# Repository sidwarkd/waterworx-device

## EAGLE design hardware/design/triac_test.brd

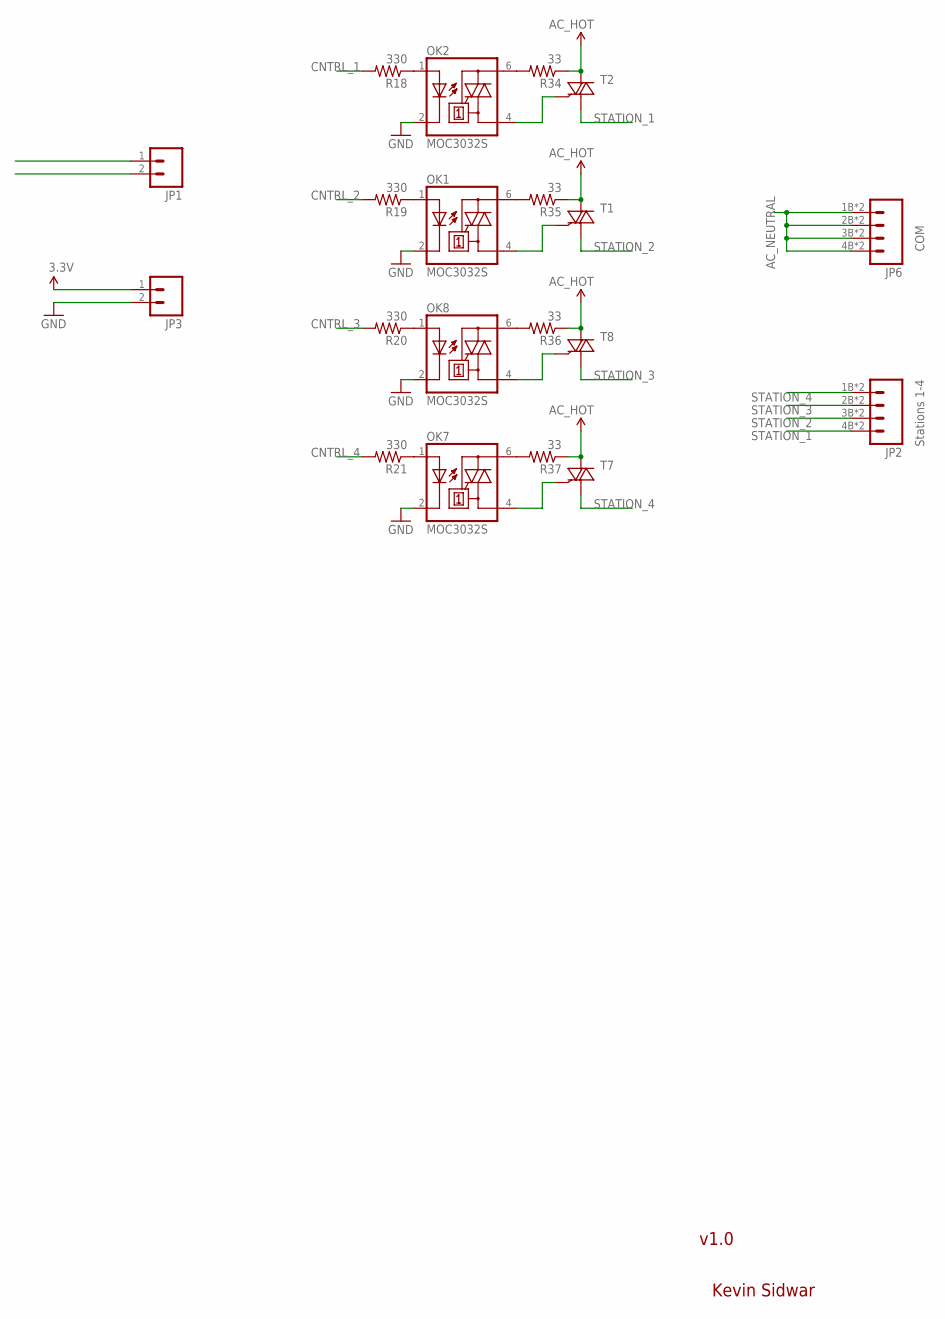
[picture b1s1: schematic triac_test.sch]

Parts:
JP1, JP3: M02LOCK; 1X02_LOCK
JP2: Stations 1-4; PHOENIX_TERMINAL_4
JP6: COM; PHOENIX_TERMINAL_4
OK1, OK2, OK7, OK8: MOC3032S; DIL6-SMD
R18, R19, R20, R21: 330; 0603-RES
R34, R35, R36, R37: 33; 0603-RES
T1, T2, T7, T8: LF-TRIACSOT223; SOT223

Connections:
3.3V: JP3.1
AC_HOT: JP1.1, R34.1, R35.1, R36.1, R37.1, T1.2 (A2), T2.2 (A2), T7.2 (A2), T8.2 (A2)
AC_NEUTRAL: JP1.2, JP6.1B (1), JP6.1T (1), JP6.2B (2), JP6.2T (2), JP6.3B (3), JP6.3T (3), JP6.4B (4), JP6.4T (4)
CNTRL_1: R18.2
CNTRL_2: R19.2
CNTRL_3: R20.2
CNTRL_4: R21.2
GND: JP3.2, OK1.2 (C), OK2.2 (C), OK7.2 (C), OK8.2 (C)
unnamed: OK1.1 (A), R19.1
unnamed: OK1.6 (A2), R35.2
unnamed: OK1.4 (A1), T1.3 (G)
unnamed: OK2.1 (A), R18.1
unnamed: OK2.6 (A2), R34.2
unnamed: OK2.4 (A1), T2.3 (G)
unnamed: OK7.1 (A), R21.1
unnamed: OK7.6 (A2), R37.2
unnamed: OK7.4 (A1), T7.3 (G)
unnamed: OK8.1 (A), R20.1
unnamed: OK8.6 (A2), R36.2
unnamed: OK8.4 (A1), T8.3 (G)
STATION_1: JP2.4B (4), JP2.4T (4), T2.1 (A1)
STATION_2: JP2.3B (3), JP2.3T (3), T1.1 (A1)
STATION_3: JP2.2B (2), JP2.2T (2), T8.1 (A1)
STATION_4: JP2.1B (1), JP2.1T (1), T7.1 (A1)

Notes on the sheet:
Kevin Sidwar
v1.0

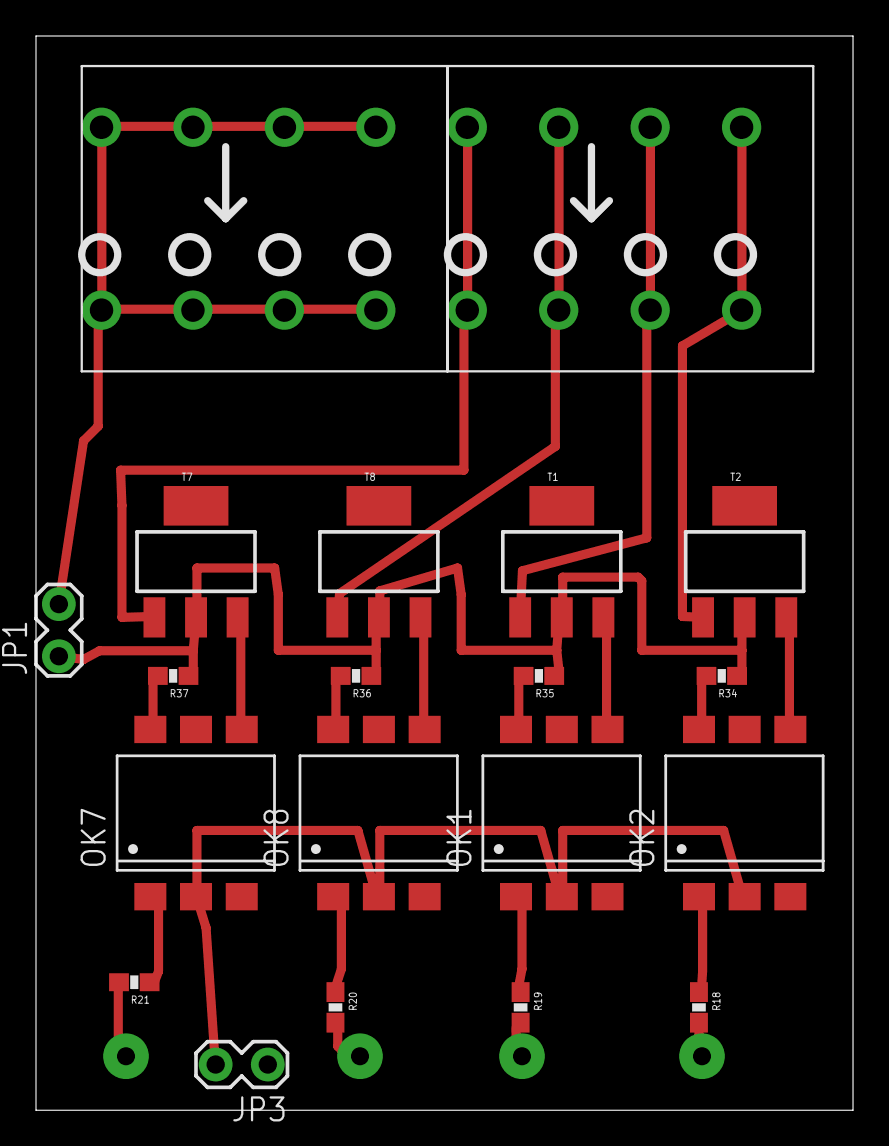
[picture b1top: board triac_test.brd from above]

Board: 2 copper layers, 45.4 x 59.7 mm, 20 parts (0 on the bottom side), 19 nets.

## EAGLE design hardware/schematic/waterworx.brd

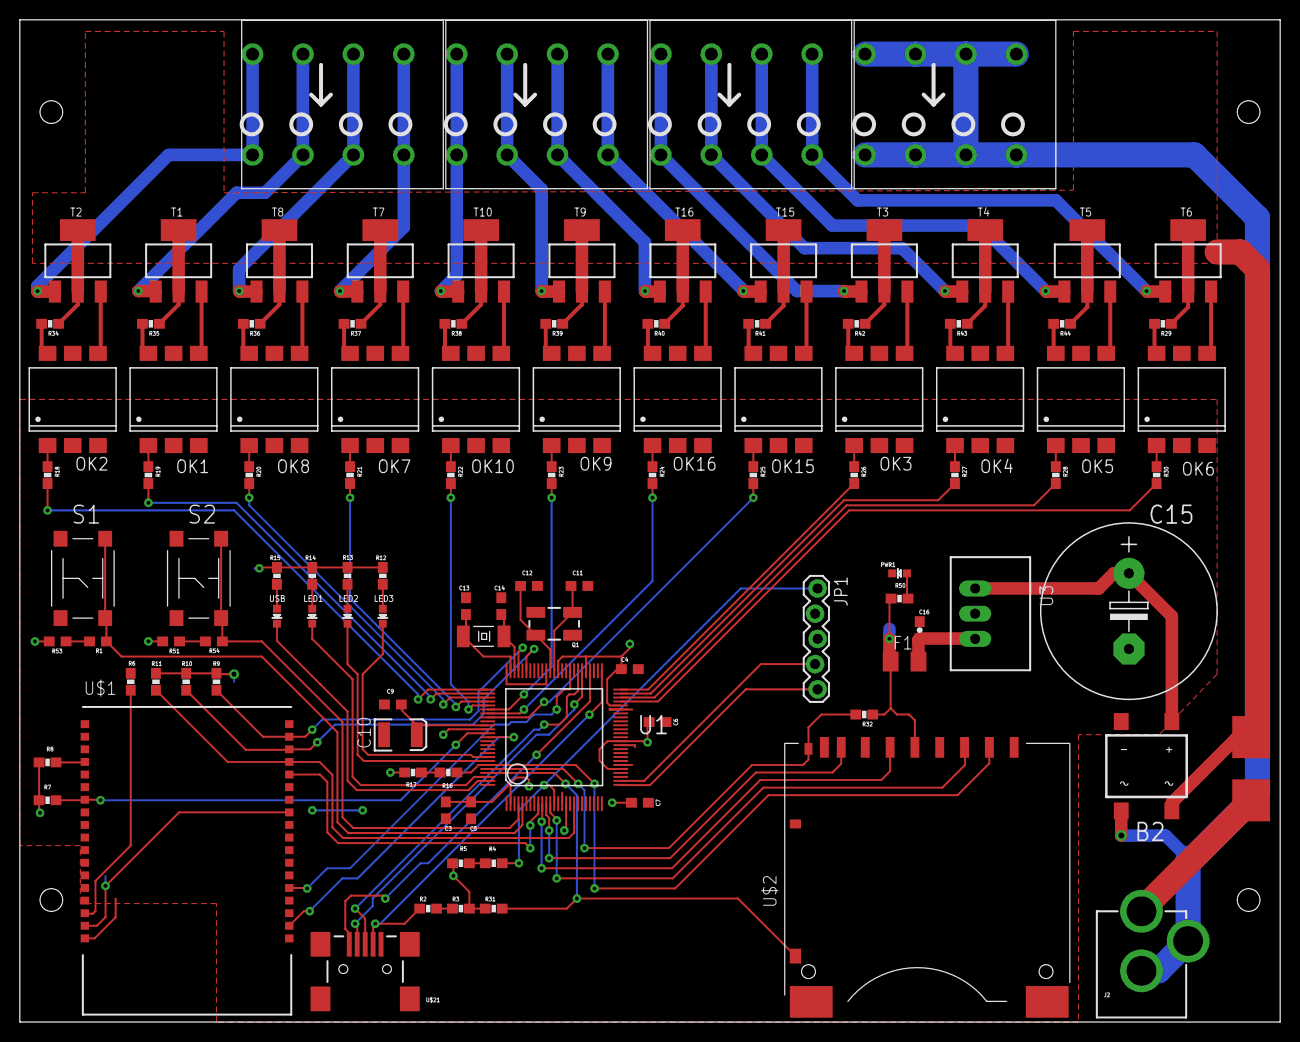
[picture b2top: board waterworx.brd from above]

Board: 2 copper layers, 127.0 x 101.0 mm, 107 parts (0 on the bottom side), 110 nets.

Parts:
B2: DF01S; DFS
C3, C4, C5, C6, C7, C9: 0.1uF; 0603
C10: 10uF; EIA3528
C11, C12: 18pF; 0603
C13, C14: 11pf; 0603
C15: 1000uF; E7,5-18
C16: 1uF; 0603-CAP
F1: 500mA PTC Fuse; M1206
F2: NANO2_HOLDER
J2: POWER_JACKPTH; POWER_JACK_PTH
JP1: 1X05_LOCK
JP2: Stations 1-4; PHOENIX_TERMINAL_4
JP3: Stations 5-8; PHOENIX_TERMINAL_4
JP4: Stations 9-12; PHOENIX_TERMINAL_4
JP6: COM; PHOENIX_TERMINAL_4
LED1: WHITE; LED-0603
LED2: RED; LED-0603
LED3: YELLOW; LED-0603
OK1, OK2, OK3, OK4, OK5, OK6, OK7, OK8, OK9, OK10, OK15, OK16: MOC3032S; DIL6-SMD
PWR1: BLUE; LED-0603
Q1: 8MHz; CRYSTAL-SMD-5X3
Q2: 32.768 KHz; CRYSTAL-SMD-4X2
R1, R51, R53, R54: 4.7K; 0603
R2, R3, R4, R5, R6, R7, R8, R9, R10, R11, R16, R17, R31, R32: 4.7K; 0603-RES
R12, R13, R14, R15, R18, R19, R20, R21, R22, R23, R24, R25, R26, R27, R28, R30, R50: 330; 0603-RES
R29, R34, R35, R36, R37, R38, R39, R40, R41, R42, R43, R44: 33; 0603-RES
S1: S1; SWITCH-OMRON
S2: SWITCH-OMRON
T1, T2, T3, T4, T5, T6, T7, T8, T9, T10, T15, T16: LF-TRIACSOT223; SOT223
U1: PIC32MX460F512L TQFP100; TQFP100
U3: RECOM_X.X_REG78XX; RECOM
U$1: MRF24WB0MA; SMD_MRF
U$2: SD_CARD_SOCKETALPS; SD_ALPS
U$21: USB-MINIB-5PIN; USB-MINIB
USB: GREEN; LED-0603

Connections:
3.3V: C3.1, C4.1, C5.1, C6.1, C7.1, F1.1, JP1.2, R3.2, R5.1, R7.2, R8.1, R9.2, R10.2, R11.2, R12.2, R13.2, R14.2, R15.2, R17.2, R31.1, R32.1, R50.2, R51.2, R53.2, U1.2, U1.16, U1.30, U1.37, U1.46, U1.55, U1.62, U1.86, U$1.17, U$1.29, U$2.4
AC_HOT: B2.AC1, F2.2, R29.1, R34.1, R35.1, R36.1, R37.1, R38.1, R39.1, R40.1, R41.1, R42.1, R43.1, R44.1, T1.2, T1.4, T2.2, T2.4, T3.2, T3.4, T4.2, T4.4, T5.2, T5.4, T6.2, T6.4, T7.2, T7.4, T8.2, T8.4, T9.2, T9.4, T10.2, T10.4, T15.2, T15.4, T16.2, T16.4
AC_NEUTRAL: B2.AC2, J2.GND, J2.GNDBREAK, JP6.1B, JP6.1T, JP6.2B, JP6.2T, JP6.3B, JP6.3T, JP6.4B, JP6.4T
CNTRL_1: R18.2, U1.76
CNTRL_2: R19.2, U1.77
CNTRL_3: R20.2, U1.78
CNTRL_4: R21.2, U1.79
CNTRL_5: R22.2, U1.80
CNTRL_6: R23.2, U1.81
CNTRL_7: R24.2, U1.82
CNTRL_8: R25.2, U1.83
CNTRL_9: R26.2, U1.50
CNTRL_10: R27.2, U1.49
CNTRL_11: R28.2, U1.48
CNTRL_12: R30.2, U1.47
D+: U1.57, U$21.D+
D-: U1.56, U$21.D-
GND: B2.-, C3.2, C4.2, C5.2, C6.2, C7.2, C9.2, C10.C, C11.1, C12.1, C13.2, C14.2, C15.-, C16.2, JP1.3, OK1.2, OK2.2, OK3.2, OK4.2, OK5.2, OK6.2, OK7.2, OK8.2, OK9.2, OK10.2, OK15.2, OK16.2, PWR1.C, R6.1, S1.1, S1.2, S2.1, S2.2, U1.15, U1.31, U1.36, U1.45, U1.65, U1.75, U3.GND, U$1.1, U$1.10, U$1.18, U$1.19, U$1.25, U$1.28, U$1.30, U$1.36, U$2.3, U$2.6, U$2.12, U$2.VSS, U$21.GND, U$21.MTN1, U$21.MTN2, U$21.MTN3, U$21.MTN4
unnamed: OK9.1, R23.1
unnamed: OK1.1, R19.1
unnamed: R51.1, R54.1
unnamed: R1.1, R53.1
unnamed: R8.2, U$1.4
unnamed: OK1.6, R35.2
unnamed: OK9.6, R39.2
unnamed: OK1.4, T1.3
unnamed: OK2.1, R18.1
unnamed: R16.1, R17.1
unnamed: R4.2, R5.2
unnamed: OK2.6, R34.2
unnamed: OK9.4, T9.3
unnamed: OK2.4, T2.3
unnamed: R2.2, R3.1
unnamed: B2.+, C15.+, U3.VIN
unnamed: OK3.1, R26.1
unnamed: OK3.6, R42.2
unnamed: PWR1.A, R50.1
unnamed: R15.1, USB.A
unnamed: OK3.4, T3.3
unnamed: LED1.A, R14.1
unnamed: LED2.A, R13.1
unnamed: C16.1, F1.2, U3.VOUT
unnamed: OK6.1, R30.1
unnamed: OK4.1, R27.1
unnamed: OK4.6, R43.2
unnamed: OK10.1, R22.1
unnamed: OK4.4, T4.3
unnamed: OK6.6, R29.2
unnamed: OK6.4, T6.3
unnamed: OK5.1, R28.1
unnamed: OK5.6, R44.2
unnamed: OK10.6, R38.2
unnamed: LED3.A, R12.1
unnamed: OK5.4, T5.3
unnamed: F2.1, J2.PWR
unnamed: OK10.4, T10.3
unnamed: OK7.1, R21.1
unnamed: OK7.6, R37.2
unnamed: OK7.4, T7.3
unnamed: OK8.1, R20.1
unnamed: OK8.6, R36.2
unnamed: OK8.4, T8.3
unnamed: OK15.1, R25.1
unnamed: OK15.6, R41.2
unnamed: OK15.4, T15.3
unnamed: OK16.1, R24.1
unnamed: OK16.6, R40.2
unnamed: OK16.4, T16.3
unnamed: C9.1, C10.A, U1.85
OSC1: C11.2, Q1.1, U1.63
OSC2: C12.2, Q1.3, U1.64
PGC: JP1.5, U1.26
PGD: JP1.4, U1.27
RC13: C14.1, Q2.P$2, U1.73
RC14: C13.1, Q2.P$1, U1.74
RE0: LED3.C, U1.93
RE1: LED2.C, U1.94
RE2: LED1.C, U1.98
RE3: U1.99, USB.C
RE6: R54.2, S2.3, S2.4, U1.4
RE7: R1.2, S1.3, S1.4, U1.5
SD_CD: R32.2, U1.96, U$2.CD
SD_CK: U1.10, U$2.5
SD_CS: R16.2, U1.95, U$2.1
SD_DI: U1.12, U$2.2
SD_DO: U1.11, U$2.7
SD_WP: R31.2, U1.97, U$2.WP
STATION_1: JP2.1B, JP2.1T, T2.1
STATION_2: JP2.2B, JP2.2T, T1.1
STATION_3: JP2.3B, JP2.3T, T8.1
STATION_4: JP2.4B, JP2.4T, T7.1
STATION_5: JP3.1B, JP3.1T, T10.1
STATION_6: JP3.2B, JP3.2T, T9.1
STATION_7: JP3.3B, JP3.3T, T16.1
STATION_8: JP3.4B, JP3.4T, T15.1
STATION_9: JP4.1B, JP4.1T, T3.1
STATION_10: JP4.2B, JP4.2T, T4.1
STATION_11: JP4.3B, JP4.3T, T5.1
STATION_12: JP4.4B, JP4.4T, T6.1
USBID: R2.1, U1.51, U$21.ID
VBUS: U1.54, U$21.VBUS
VPP: JP1.1, R4.1, U1.13
WF_CK: R10.1, U1.70, U$1.34
WF_CS: U1.59, U$1.23
WF_DI: R9.1, U1.72, U$1.35
WF_DO: U1.9, U$1.32
WF_HIBERNATE: U1.88, U$1.20
WF_INT: R11.1, U1.18, U$1.33
WF_RESET: R7.1, U1.87, U$1.7
WF_WP: R6.2, U$1.16

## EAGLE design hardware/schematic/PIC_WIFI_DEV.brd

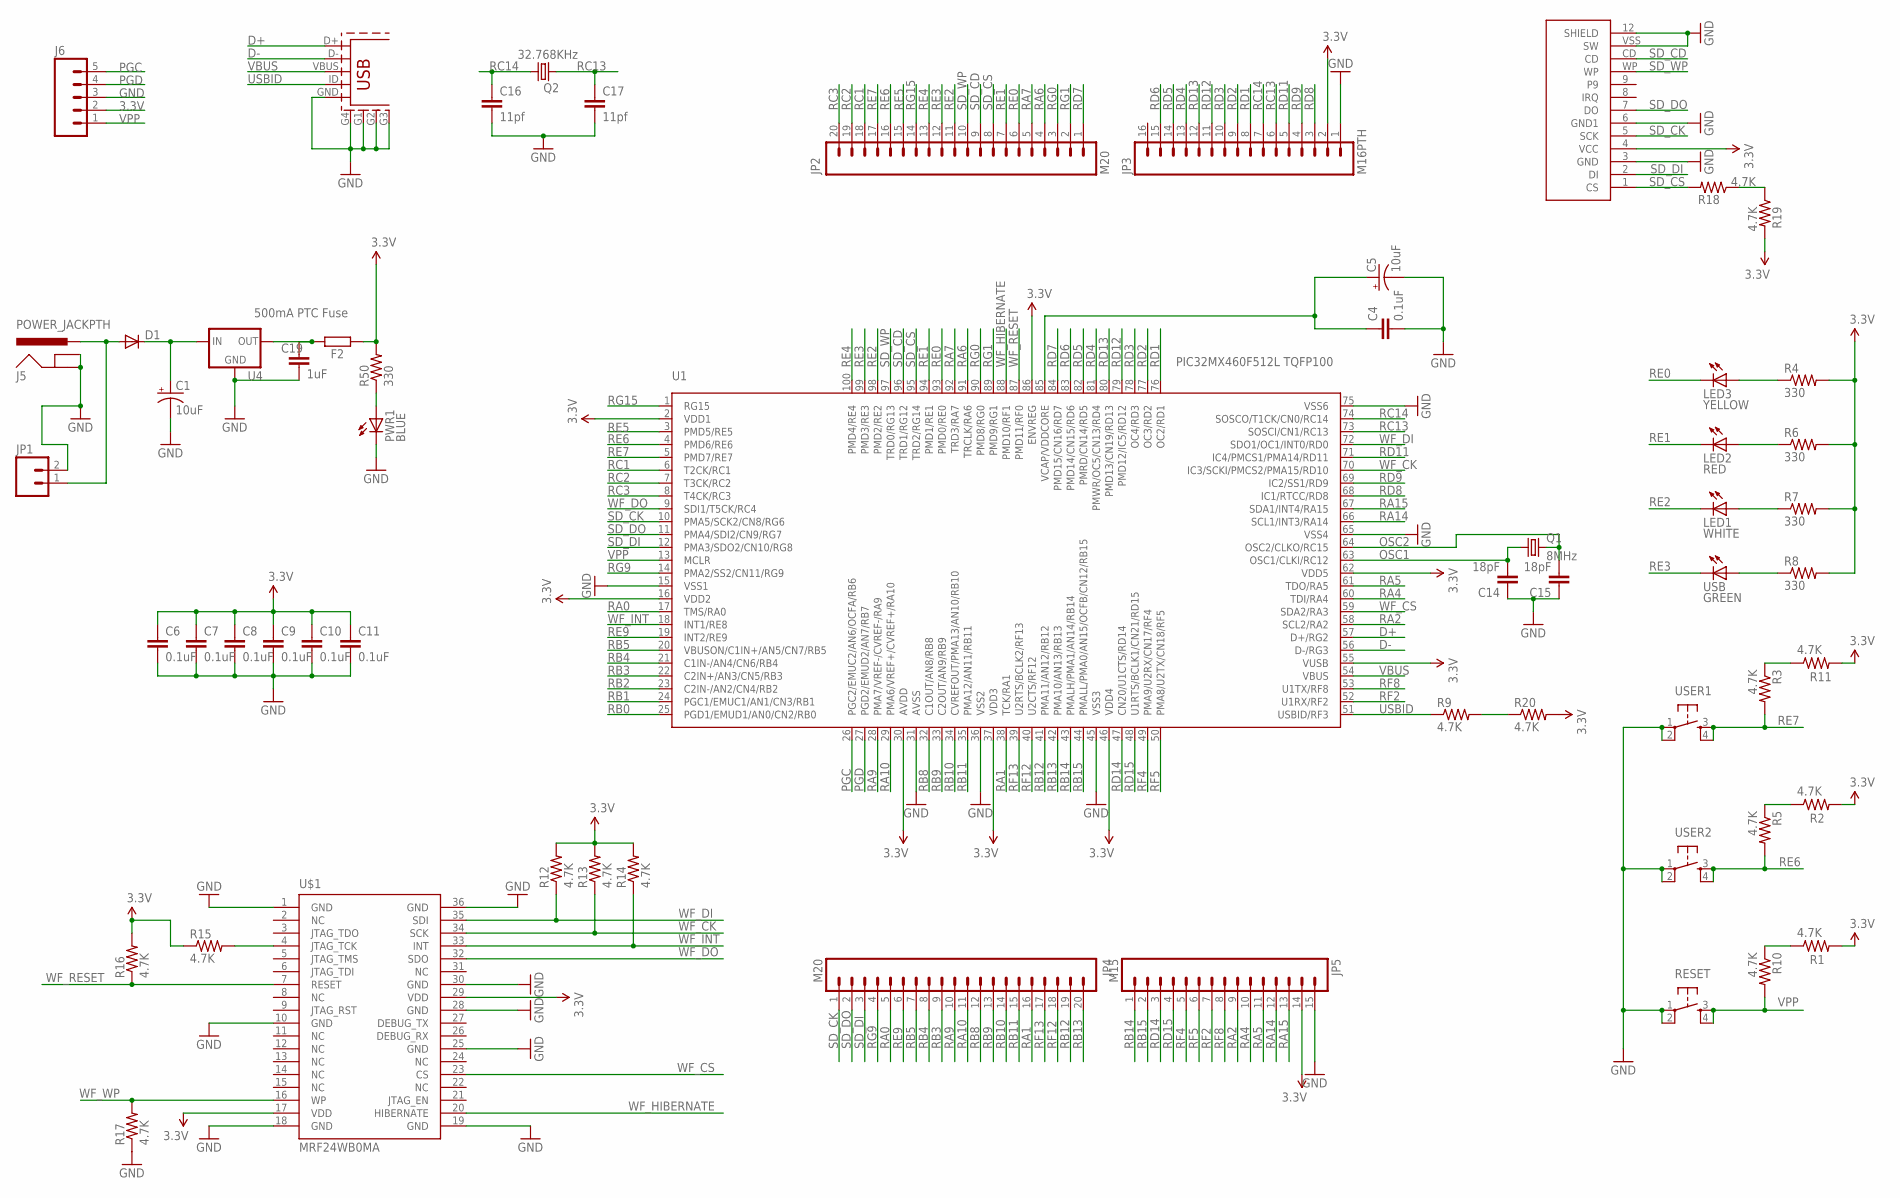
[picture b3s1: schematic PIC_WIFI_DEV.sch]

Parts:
C1, C5: 10uF; EIA3528
C4, C6, C7, C8, C9, C10, C11: 0.1uF; C0402
C14, C15: 18pF; C0402
C16, C17: 11pf; C0402
C19: 1uF; 0603-CAP
D1: DIODESMA; SMA-DIODE
F2: 500mA PTC Fuse; M1206
J5: POWER_JACKPTH; POWER_JACK_PTH
J6: M05PTH; 1X05
J8: USB_5PIN; USB-MINIB
JP1: M02PTH; 1X02
JP2, JP4: M20; 1X20
JP3: M16PTH; 1X16
JP5: M15; 1X15
LED1: WHITE; LED-0603
LED2: RED; LED-0603
LED3: YELLOW; LED-0603
PWR1: BLUE; LED-0603
Q1: 8MHz; CRYSTAL-SMD-5X3
Q2: 32.768KHz; CRYSTAL-SMD-4X2
R1, R2, R3, R5, R9, R10, R11, R20: 4.7K; C0402
R4, R6, R7, R8: 330; C0402
R12, R13, R14, R15, R16, R17, R18, R19: 4.7K; 0603-RES
R50: 330; 0603-RES
RESET: TAC_SWITCHB3FS; SWITCH-OMRON
U1: PIC32MX460F512L TQFP100; TQFP100
U4: RECOM_X.X_REG78XX; RECOM
U$1: MRF24WB0MA; SMD_MRF
U$2: SD_CARD_SOCKETALPS; SD_ALPS
USB: GREEN; LED-0603
USER1, USER2: TAC_SWITCHB3FS; SWITCH-OMRON

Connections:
3.3V: C6.1, C7.1, C8.1, C9.1, C10.1, C11.1, F2.1, J6.2, JP3.2, JP5.14, R1.2, R2.2, R4.2, R6.2, R7.2, R8.2, R11.2, R12.2, R13.2, R14.2, R15.1, R16.2, R19.2, R20.2, R50.2, U1.2 (VDD1), U1.16 (VDD2), U1.30 (AVDD), U1.37 (VDD3), U1.46 (VDD4), U1.55 (VUSB), U1.62 (VDD5), U1.86 (ENVREG), U$1.17 (VDD), U$1.29 (VDD), U$2.4 (VCC)
D+: J8.D+, U1.57 (D+/RG2)
D-: J8.D-, U1.56 (D-/RG3)
GND: C1.C (-), C4.2, C5.C (-), C6.2, C7.2, C8.2, C9.2, C10.2, C11.2, C14.1, C15.1, C16.2, C17.2, C19.2, J5.GND, J5.GNDBREAK, J6.3, J8.G1, J8.G2, J8.G3, J8.G4 (SHIELD), J8.GND, JP1.2, JP3.1, JP5.15, PWR1.C, R17.1, RESET.1, RESET.2, U1.15 (VSS1), U1.31 (AVSS), U1.36 (VSS2), U1.45 (VSS3), U1.65 (VSS4), U1.75 (VSS6), U4.GND, U$1.1 (GND), U$1.10 (GND), U$1.18 (GND), U$1.19 (GND), U$1.25 (GND), U$1.28 (GND), U$1.30 (GND), U$1.36 (GND), U$2.3 (GND), U$2.6 (GND1), U$2.12 (SHIELD), U$2.VSS (SW), USER1.1, USER1.2, USER2.1, USER2.2
unnamed: R1.1, R10.1
unnamed: D1.A, J5.PWR, JP1.1
unnamed: R2.1, R5.1
unnamed: R3.1, R11.1
unnamed: R15.2, U$1.4 (JTAG_TCK)
unnamed: R9.2, R20.1
unnamed: R18.1, R19.1
unnamed: PWR1.A, R50.1
unnamed: R8.1, USB.A
unnamed: LED1.A, R7.1
unnamed: LED2.A, R6.1
unnamed: C19.1, F2.2, U4.VOUT (OUT)
unnamed: LED3.A, R4.1
unnamed: C4.1, C5.A (+), U1.85 (VCAP/VDDCORE)
OSC1: C14.2, Q1.1, U1.63 (OSC1/CLKI/RC12)
OSC2: C15.2, Q1.3 (2), U1.64 (OSC2/CLKO/RC15)
PGC: J6.5, U1.26 (PGC2/EMUC2/AN6/OCFA/RB6)
PGD: J6.4, U1.27 (PGD2/EMUD2/AN7/RB7)
RA0: JP4.5, U1.17 (TMS/RA0)
RA1: JP4.16, U1.38 (TCK/RA1)
RA2: JP5.9, U1.58 (SCL2/RA2)
RA4: JP5.10, U1.60 (TDI/RA4)
RA5: JP5.11, U1.61 (TDO/RA5)
RA6: JP2.4, U1.91 (TRCLK/RA6)
RA7: JP2.5, U1.92 (TRD3/RA7)
RA9: JP4.10, U1.28 (PMA7/VREF-/CVREF-/RA9)
RA10: JP4.11, U1.29 (PMA6/VREF+/CVREF+/RA10)
RA14: JP5.12, U1.66 (SCL1/INT3/RA14)
RA15: JP5.13, U1.67 (SDA1/INT4/RA15)
RB0: U1.25 (PGD1/EMUD1/AN0/CN2/RB0)
RB1: U1.24 (PGC1/EMUC1/AN1/CN3/RB1)
RB2: U1.23 (C2IN-/AN2/CN4/RB2)
RB3: JP4.9, U1.22 (C2IN+/AN3/CN5/RB3)
RB4: JP4.8, U1.21 (C1IN-/AN4/CN6/RB4)
RB5: JP4.7, U1.20 (VBUSON/C1IN+/AN5/CN7/RB5)
RB8: JP4.12, U1.32 (C1OUT/AN8/RB8)
RB9: JP4.13, U1.33 (C2OUT/AN9/RB9)
RB10: JP4.14, U1.34 (CVREFOUT/PMA13/AN10/RB10)
RB11: JP4.15, U1.35 (PMA12/AN11/RB11)
RB12: JP4.19, U1.41 (PMA11/AN12/RB12)
RB13: JP4.20, U1.42 (PMA10/AN13/RB13)
RB14: JP5.1, U1.43 (PMALH/PMA1/AN14/RB14)
RB15: JP5.2, U1.44 (PMALL/PMA0/AN15/OCFB/CN12/RB15)
RC1: JP2.18, U1.6 (T2CK/RC1)
RC2: JP2.19, U1.7 (T3CK/RC2)
RC3: JP2.20, U1.8 (T4CK/RC3)
RC13: C17.1, JP3.6, Q2.P$2 (2), U1.73 (SOSCI/CN1/RC13)
RC14: C16.1, JP3.7, Q2.P$1 (1), U1.74 (SOSCO/T1CK/CN0/RC14)
RD1: JP3.8, U1.76 (OC2/RD1)
RD2: JP3.9, U1.77 (OC3/RD2)
RD3: JP3.10, U1.78 (OC4/RD3)
RD4: JP3.13, U1.81 (PMWR/OC5/CN13/RD4)
RD5: JP3.14, U1.82 (PMRD/CN14/RD5)
RD6: JP3.15, U1.83 (PMD14/CN15/RD6)
RD7: JP2.1, U1.84 (PMD15/CN16/RD7)
RD8: JP3.3, U1.68 (IC1/RTCC/RD8)
RD9: JP3.4, U1.69 (IC2/SS1/RD9)
RD11: JP3.5, U1.71 (IC4/PMCS1/PMA14/RD11)
RD12: JP3.11, U1.79 (PMD12/IC5/RD12)
RD13: JP3.12, U1.80 (PMD13/CN19/RD13)
RD14: JP5.3, U1.47 (CN20/U1CTS/RD14)
RD15: JP5.4, U1.48 (U1RTS/BCLK1/CN21/RD15)
RE0: JP2.6, LED3.C, U1.93 (PMD0/RE0)
RE1: JP2.7, LED2.C, U1.94 (PMD1/RE1)
RE2: JP2.11, LED1.C, U1.98 (PMD2/RE2)
RE3: JP2.12, U1.99 (PMD3/RE3), USB.C
RE4: JP2.13, U1.100 (PMD4/RE4)
RE5: JP2.15, U1.3 (PMD5/RE5)
RE6: JP2.16, R5.2, U1.4 (PMD6/RE6), USER2.3, USER2.4
RE7: JP2.17, R3.2, U1.5 (PMD7/RE7), USER1.3, USER1.4
RE9: JP4.6, U1.19 (INT2/RE9)
RF2: JP5.7, U1.52 (U1RX/RF2)
RF4: JP5.5, U1.49 (PMA9/U2RX/CN17/RF4)
RF5: JP5.6, U1.50 (PMA8/U2TX/CN18/RF5)
RF8: JP5.8, U1.53 (U1TX/RF8)
RF12: JP4.18, U1.40 (U2CTS/RF12)
RF13: JP4.17, U1.39 (U2RTS/BCLK2/RF13)
RG0: JP2.3, U1.90 (PMD8/RG0)
RG1: JP2.2, U1.89 (PMD9/RG1)
RG9: JP4.4, U1.14 (PMA2/SS2/CN11/RG9)
RG15: JP2.14, U1.1 (RG15)
SD_CD: JP2.9, U1.96 (TRD1/RG12), U$2.CD
SD_CK: JP4.1, U1.10 (PMA5/SCK2/CN8/RG6), U$2.5 (SCK)
SD_CS: JP2.8, R18.2, U1.95 (TRD2/RG14), U$2.1 (CS)
SD_DI: JP4.3, U1.12 (PMA3/SDO2/CN10/RG8), U$2.2 (DI)
SD_DO: JP4.2, U1.11 (PMA4/SDI2/CN9/RG7), U$2.7 (DO)
SD_WP: JP2.10, U1.97 (TRD0/RG13), U$2.WP
USBID: J8.ID (USB_ID), R9.1, U1.51 (USBID/RF3)
VBUS: J8.VBUS, U1.54 (VBUS)
VIN_RAW: C1.A (+), D1.C, U4.VIN (IN)
VPP: J6.1, R10.2, RESET.3, RESET.4, U1.13 (MCLR)
WF_CK: R13.1, U1.70 (IC3/SCKI/PMCS2/PMA15/RD10), U$1.34 (SCK)
WF_CS: U1.59 (SDA2/RA3), U$1.23 (CS)
WF_DI: R12.1, U1.72 (SDO1/OC1/INT0/RD0), U$1.35 (SDI)
WF_DO: U1.9 (SDI1/T5CK/RC4), U$1.32 (SDO)
WF_HIBERNATE: U1.88 (PMD10/RF1), U$1.20 (HIBERNATE)
WF_INT: R14.1, U1.18 (INT1/RE8), U$1.33 (INT)
WF_RESET: R16.1, U1.87 (PMD11/RF0), U$1.7 (RESET)
WF_WP: R17.2, U$1.16 (WP)

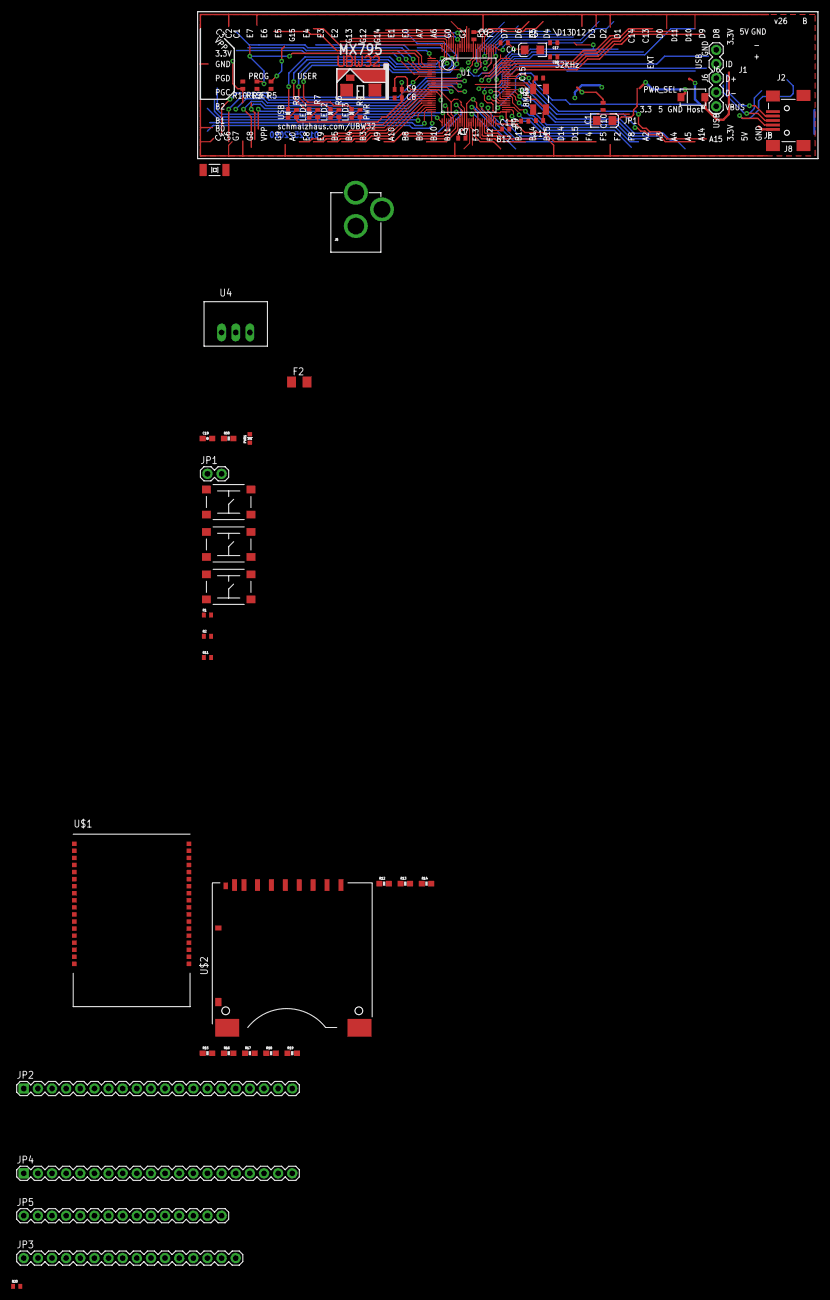
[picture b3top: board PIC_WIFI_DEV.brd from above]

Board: 2 copper layers, 111.5 x 26.4 mm, 61 parts (0 on the bottom side), 100 nets.

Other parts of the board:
U$3: UBW32
U$5: SCHMALZHAUS

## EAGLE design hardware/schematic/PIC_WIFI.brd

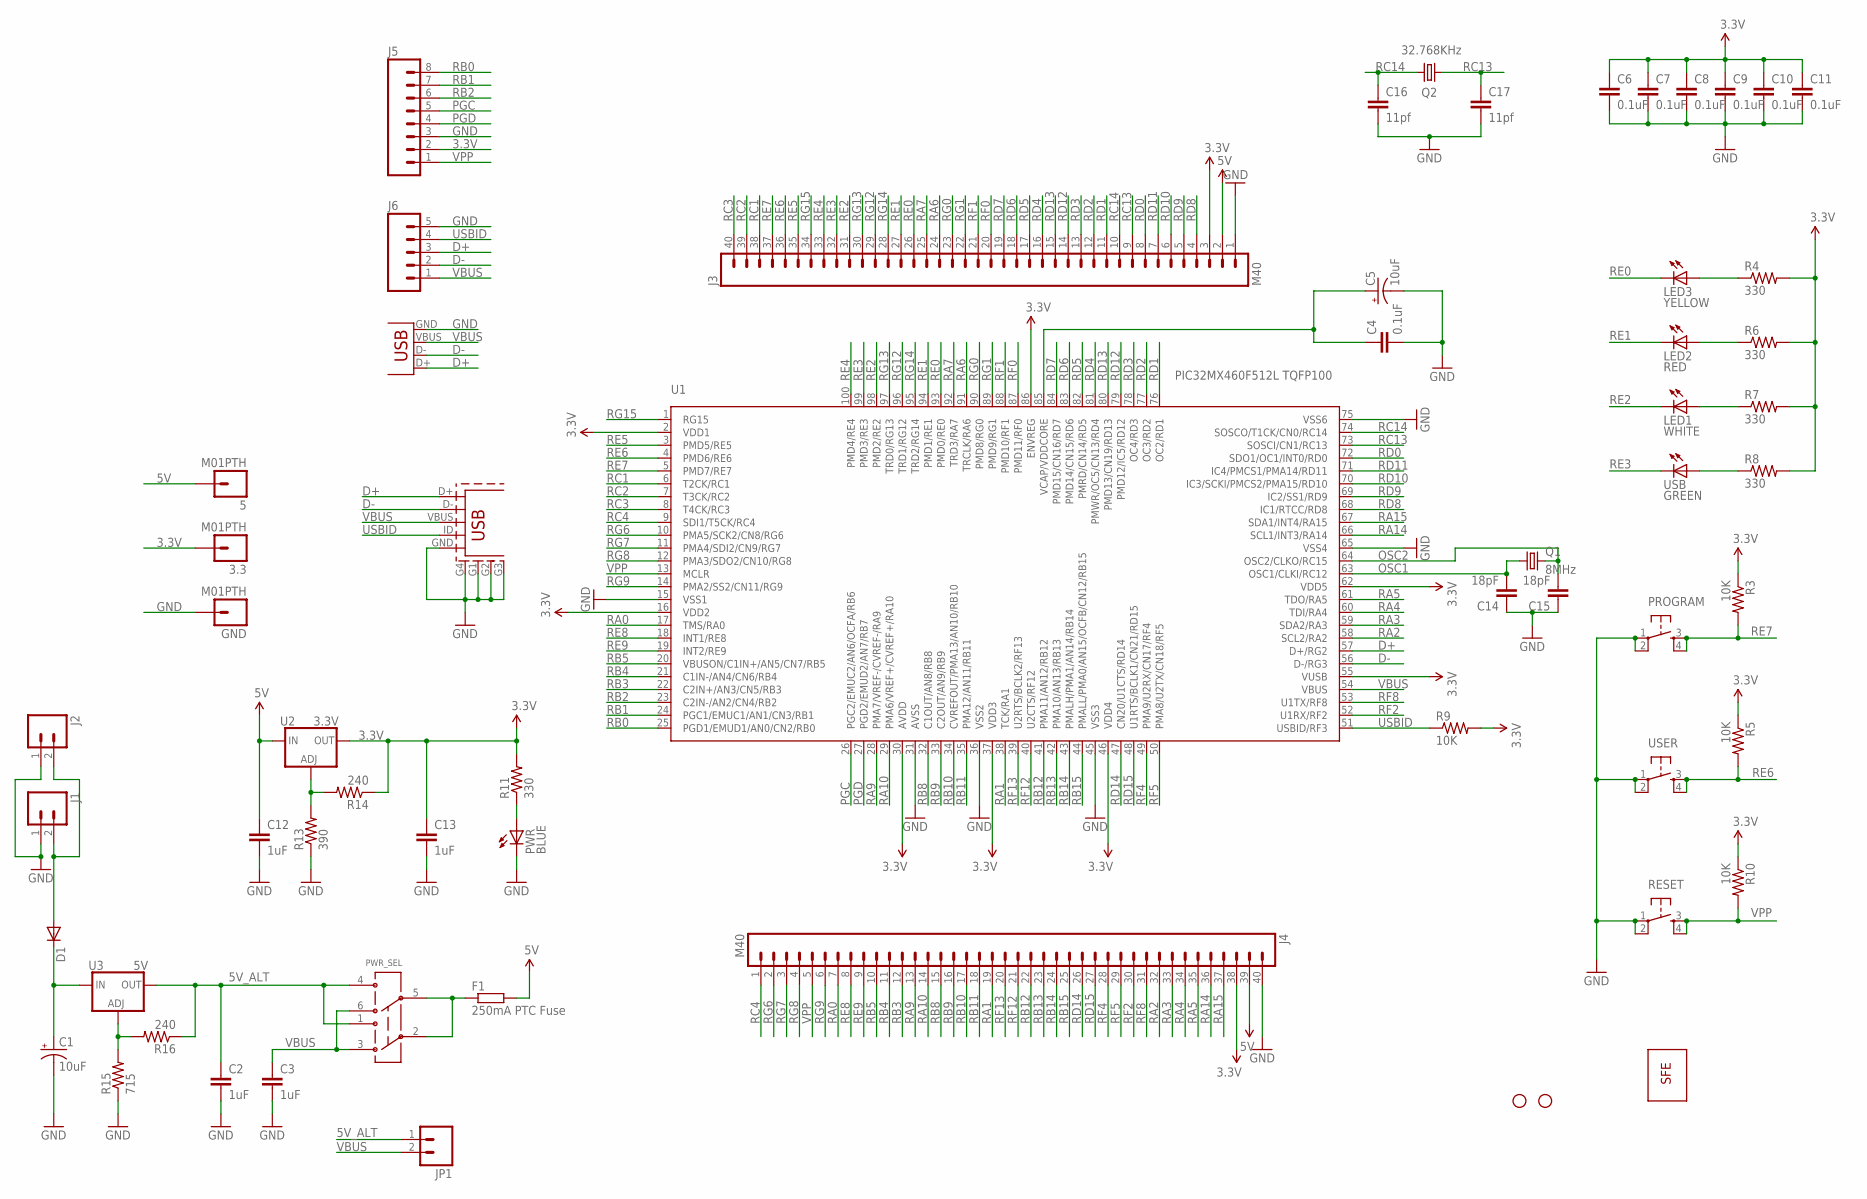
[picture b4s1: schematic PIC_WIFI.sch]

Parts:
3.3, 5: M01PTH; 1X01
C1, C5: 10uF; EIA3528
C2, C3, C12, C13: 1uF; C0402
C4, C6, C7, C8, C9, C10, C11: 0.1uF; C0402
C14, C15: 18pF; C0402
C16, C17: 11pf; C0402
D1: DIODESMA; SMA-DIODE
F1: 250mA PTC Fuse; R1206
GND: M01PTH; 1X01
J1: M02PTH; 1X02
J2: M02-JST-2MM-SMT; S2B-PH
J3, J4: M40; 1X40
J5: M08; 1X08
J6: M05PTH; 1X05
J7: USB-A-S
J8: USB_5PIN; USB-MINIB
JP1: M02PTH; 1X02
LED1: WHITE; LED-0603
LED2: RED; LED-0603
LED3: YELLOW; LED-0603
PROGRAM: TAC_SWITCHSND; TACTILE_SWITCH_SMD
PWR: BLUE; LED-0603
PWR_SEL: AYZ0202
Q1: 8MHz; CRYSTAL-SMD-5X3
Q2: 32.768KHz; CRYSTAL-32KHZ-SMD
R3, R5, R9, R10: 10K; C0402
R4, R6, R7, R8, R11: 330; C0402
R13: 390; C0402
R14, R16: 240; C0402
R15: 715; C0402
RESET: TAC_SWITCHSND; TACTILE_SWITCH_SMD
U1: PIC32MX460F512L TQFP100; TQFP100
U2: 3.3V; SOT223
U3: 5V; SOT223
U$4: LOGO-SFENEW; SFE-NEW-WEBLOGO
U$6, U$7: STAND-OFF
USB: GREEN; LED-0603
USER: TAC_SWITCHSND; TACTILE_SWITCH_SMD

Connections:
3.3V: 3.3.1, C6.1, C7.1, C8.1, C9.1, C10.1, C11.1, C13.1, J3.3, J4.38, J5.2, R3.1, R4.2, R5.1, R6.2, R7.2, R8.2, R9.2, R10.1, R11.2, R14.1, U1.2 (VDD1), U1.16 (VDD2), U1.30 (AVDD), U1.37 (VDD3), U1.46 (VDD4), U1.55 (VUSB), U1.62 (VDD5), U1.86 (ENVREG), U2.2 (OUT)
5V: 5.1, C12.1, F1.2, J3.2, J4.39, U2.3 (IN)
5V_ALT: C2.1, JP1.1, PWR_SEL.1 (3), PWR_SEL.4 (6), R16.1, U3.2 (OUT)
D+: J6.3, J7.D+, J8.D+, U1.57 (D+/RG2)
D-: J6.2, J7.D-, J8.D-, U1.56 (D-/RG3)
GND: C1.C (-), C2.2, C3.2, C4.2, C5.C (-), C6.2, C7.2, C8.2, C9.2, C10.2, C11.2, C12.2, C13.2, C14.1, C15.1, C16.2, C17.2, GND.1, J1.1, J2.1, J3.1, J4.40, J5.3, J6.5, J7.GND, J8.G1, J8.G2, J8.G3, J8.G4 (SHIELD), J8.GND, PROGRAM.1, PROGRAM.2, PWR.C, R13.1, R15.1, RESET.1, RESET.2, U1.15 (VSS1), U1.31 (AVSS), U1.36 (VSS2), U1.45 (VSS3), U1.65 (VSS4), U1.75 (VSS6), USER.1, USER.2
unnamed: D1.A, J1.2, J2.2
unnamed: F1.1, PWR_SEL.2, PWR_SEL.5
unnamed: R13.2, R14.2, U2.1 (ADJ)
unnamed: R15.2, R16.2, U3.1 (ADJ)
unnamed: PWR.A, R11.1
unnamed: R8.1, USB.A
unnamed: LED1.A, R7.1
unnamed: LED2.A, R6.1
unnamed: LED3.A, R4.1
unnamed: C4.1, C5.A (+), U1.85 (VCAP/VDDCORE)
OSC1: C14.2, Q1.1, U1.63 (OSC1/CLKI/RC12)
OSC2: C15.2, Q1.3 (2), U1.64 (OSC2/CLKO/RC15)
PGC: J5.5, U1.26 (PGC2/EMUC2/AN6/OCFA/RB6)
PGD: J5.4, U1.27 (PGD2/EMUD2/AN7/RB7)
RA0: J4.7, U1.17 (TMS/RA0)
RA1: J4.19, U1.38 (TCK/RA1)
RA2: J4.32, U1.58 (SCL2/RA2)
RA3: J4.33, U1.59 (SDA2/RA3)
RA4: J4.34, U1.60 (TDI/RA4)
RA5: J4.35, U1.61 (TDO/RA5)
RA6: J3.24, U1.91 (TRCLK/RA6)
RA7: J3.25, U1.92 (TRD3/RA7)
RA9: J4.13, U1.28 (PMA7/VREF-/CVREF-/RA9)
RA10: J4.14, U1.29 (PMA6/VREF+/CVREF+/RA10)
RA14: J4.36, U1.66 (SCL1/INT3/RA14)
RA15: J4.37, U1.67 (SDA1/INT4/RA15)
RB0: J5.8, U1.25 (PGD1/EMUD1/AN0/CN2/RB0)
RB1: J5.7, U1.24 (PGC1/EMUC1/AN1/CN3/RB1)
RB2: J5.6, U1.23 (C2IN-/AN2/CN4/RB2)
RB3: J4.12, U1.22 (C2IN+/AN3/CN5/RB3)
RB4: J4.11, U1.21 (C1IN-/AN4/CN6/RB4)
RB5: J4.10, U1.20 (VBUSON/C1IN+/AN5/CN7/RB5)
RB8: J4.15, U1.32 (C1OUT/AN8/RB8)
RB9: J4.16, U1.33 (C2OUT/AN9/RB9)
RB10: J4.17, U1.34 (CVREFOUT/PMA13/AN10/RB10)
RB11: J4.18, U1.35 (PMA12/AN11/RB11)
RB12: J4.22, U1.41 (PMA11/AN12/RB12)
RB13: J4.23, U1.42 (PMA10/AN13/RB13)
RB14: J4.24, U1.43 (PMALH/PMA1/AN14/RB14)
RB15: J4.25, U1.44 (PMALL/PMA0/AN15/OCFB/CN12/RB15)
RC1: J3.38, U1.6 (T2CK/RC1)
RC2: J3.39, U1.7 (T3CK/RC2)
RC3: J3.40, U1.8 (T4CK/RC3)
RC4: J4.1, U1.9 (SDI1/T5CK/RC4)
RC13: C17.1, J3.9, Q2.X1 (1), U1.73 (SOSCI/CN1/RC13)
RC14: C16.1, J3.10, Q2.X2 (2), U1.74 (SOSCO/T1CK/CN0/RC14)
RD0: J3.8, U1.72 (SDO1/OC1/INT0/RD0)
RD1: J3.11, U1.76 (OC2/RD1)
RD2: J3.12, U1.77 (OC3/RD2)
RD3: J3.13, U1.78 (OC4/RD3)
RD4: J3.16, U1.81 (PMWR/OC5/CN13/RD4)
RD5: J3.17, U1.82 (PMRD/CN14/RD5)
RD6: J3.18, U1.83 (PMD14/CN15/RD6)
RD7: J3.19, U1.84 (PMD15/CN16/RD7)
RD8: J3.4, U1.68 (IC1/RTCC/RD8)
RD9: J3.5, U1.69 (IC2/SS1/RD9)
RD10: J3.6, U1.70 (IC3/SCKI/PMCS2/PMA15/RD10)
RD11: J3.7, U1.71 (IC4/PMCS1/PMA14/RD11)
RD12: J3.14, U1.79 (PMD12/IC5/RD12)
RD13: J3.15, U1.80 (PMD13/CN19/RD13)
RD14: J4.26, U1.47 (CN20/U1CTS/RD14)
RD15: J4.27, U1.48 (U1RTS/BCLK1/CN21/RD15)
RE0: J3.26, LED3.C, U1.93 (PMD0/RE0)
RE1: J3.27, LED2.C, U1.94 (PMD1/RE1)
RE2: J3.31, LED1.C, U1.98 (PMD2/RE2)
RE3: J3.32, U1.99 (PMD3/RE3), USB.C
RE4: J3.33, U1.100 (PMD4/RE4)
RE5: J3.35, U1.3 (PMD5/RE5)
RE6: J3.36, R5.2, U1.4 (PMD6/RE6), USER.3, USER.4
RE7: J3.37, PROGRAM.3, PROGRAM.4, R3.2, U1.5 (PMD7/RE7)
RE8: J4.8, U1.18 (INT1/RE8)
RE9: J4.9, U1.19 (INT2/RE9)
RF0: J3.20, U1.87 (PMD11/RF0)
RF1: J3.21, U1.88 (PMD10/RF1)
RF2: J4.30, U1.52 (U1RX/RF2)
RF4: J4.28, U1.49 (PMA9/U2RX/CN17/RF4)
RF5: J4.29, U1.50 (PMA8/U2TX/CN18/RF5)
RF8: J4.31, U1.53 (U1TX/RF8)
RF12: J4.21, U1.40 (U2CTS/RF12)
RF13: J4.20, U1.39 (U2RTS/BCLK2/RF13)
RG0: J3.23, U1.90 (PMD8/RG0)
RG1: J3.22, U1.89 (PMD9/RG1)
RG6: J4.2, U1.10 (PMA5/SCK2/CN8/RG6)
RG7: J4.3, U1.11 (PMA4/SDI2/CN9/RG7)
RG8: J4.4, U1.12 (PMA3/SDO2/CN10/RG8)
RG9: J4.6, U1.14 (PMA2/SS2/CN11/RG9)
RG12: J3.29, U1.96 (TRD1/RG12)
RG13: J3.30, U1.97 (TRD0/RG13)
RG14: J3.28, U1.95 (TRD2/RG14)
RG15: J3.34, U1.1 (RG15)
USBID: J6.4, J8.ID (USB_ID), R9.1, U1.51 (USBID/RF3)
VBUS: C3.1, J6.1, J7.VBUS, J8.VBUS, JP1.2, PWR_SEL.3 (1), PWR_SEL.6 (4), U1.54 (VBUS)
VIN_RAW: C1.A (+), D1.C, U3.3 (IN)
VPP: J4.5, J5.1, R10.2, RESET.3, RESET.4, U1.13 (MCLR)

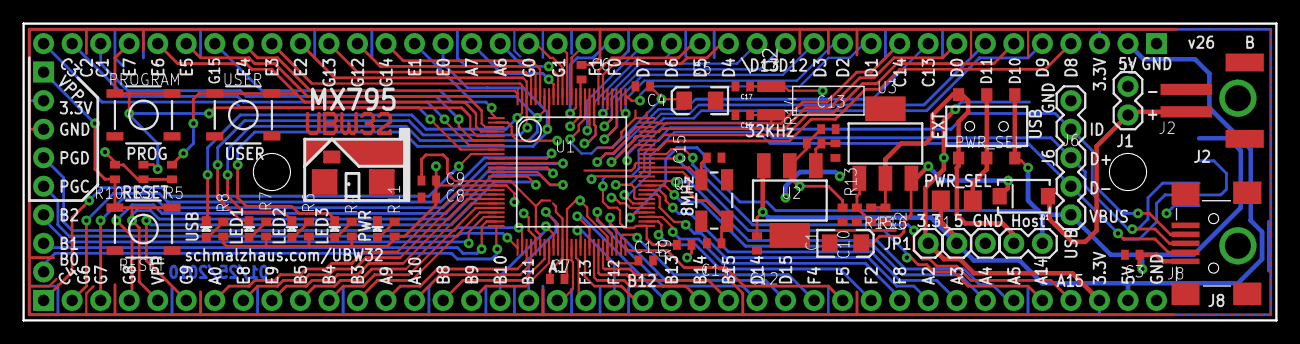
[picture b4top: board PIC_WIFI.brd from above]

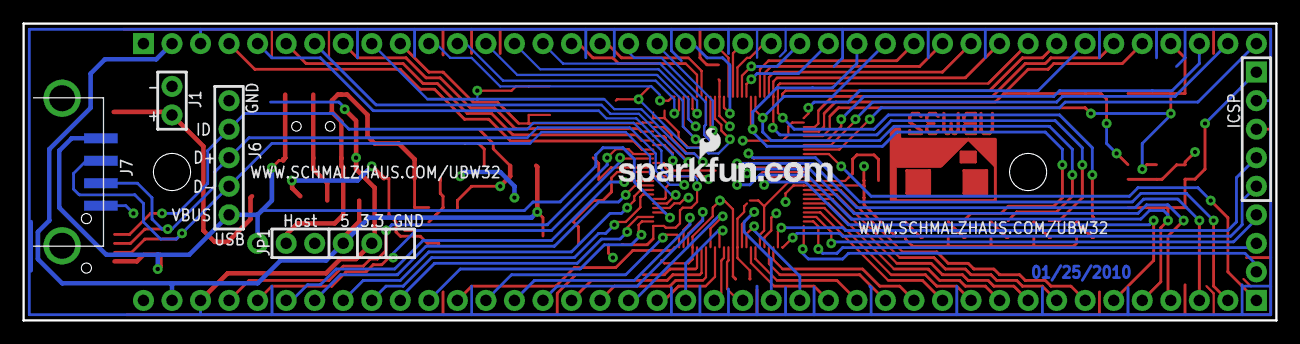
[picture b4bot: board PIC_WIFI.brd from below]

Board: 2 copper layers, 111.5 x 26.4 mm, 63 parts (2 on the bottom side), 100 nets.

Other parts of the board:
U$3: UBW32
U$5: SCHMALZHAUS

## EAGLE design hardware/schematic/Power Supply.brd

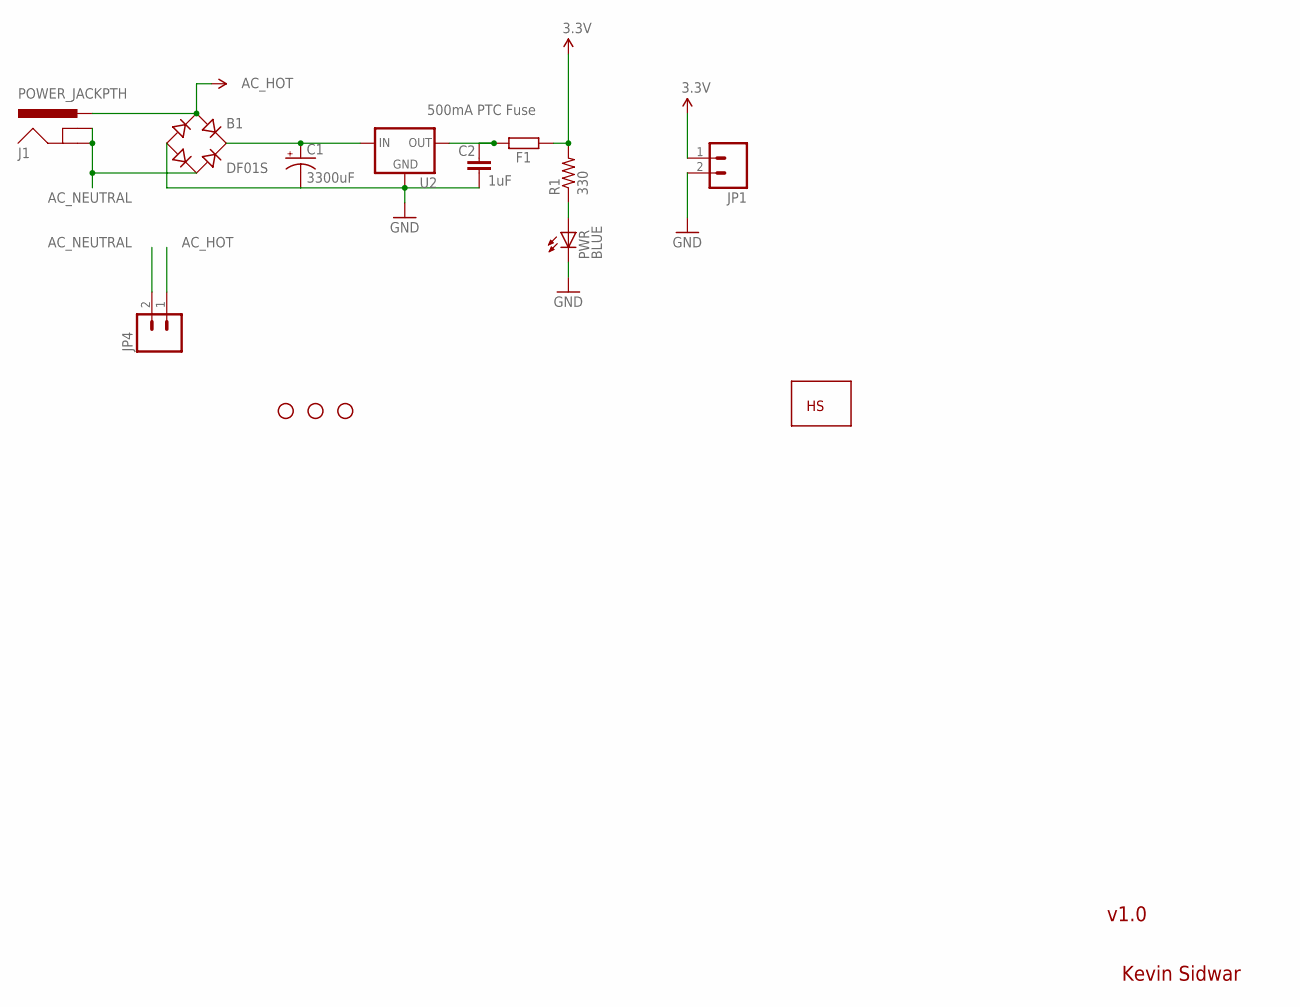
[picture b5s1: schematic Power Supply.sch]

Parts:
B1: DF01S; DFS
C1: 3300uF; EB20D
C2: 1uF; 0603-CAP
F1: 500mA PTC Fuse; M1206
J1: POWER_JACKPTH; POWER_JACK_PTH
JP1, JP4: M02LOCK_LONGPADS; 1X02_LOCK_LONGPADS
JP5, JP6, JP8: STAND-OFF
PWR: BLUE; LED-0603
R1: 330; 0603-RES
U2: RECOM_X.X_REG78XX; RECOM
U$1: LOGONORMAL; HS_LOGO

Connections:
3.3V: F1.1, JP1.1, R1.2
AC_HOT: B1.AC1, J1.PWR, JP4.1
AC_NEUTRAL: B1.AC2, J1.GND, J1.GNDBREAK, JP4.2
GND: B1.-, C1.-, C2.2, JP1.2, PWR.C, U2.GND
unnamed: C2.1, F1.2, U2.VOUT (OUT)
unnamed: B1.+, C1.+, U2.VIN (IN)
unnamed: PWR.A, R1.1

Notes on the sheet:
Kevin Sidwar
v1.0

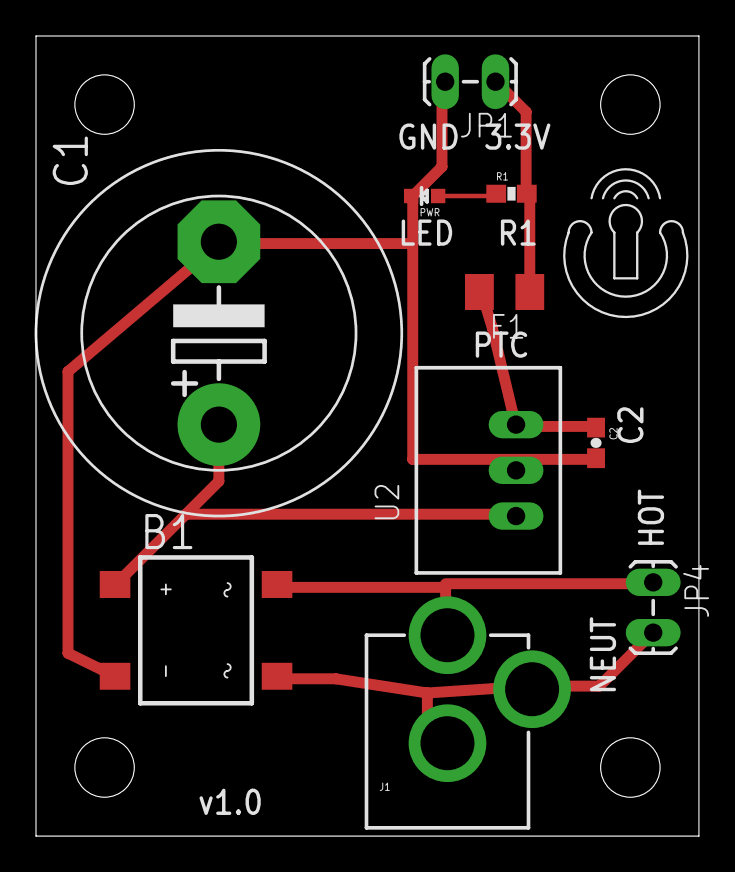
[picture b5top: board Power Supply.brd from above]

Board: 2 copper layers, 36.8 x 44.5 mm, 15 parts (0 on the bottom side), 7 nets.

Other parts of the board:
JP7: STAND-OFF

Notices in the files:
hardware/schematic/PIC_WIFI.sch:
licenced under Creative Commons v3.0 Attribution licence
parts and their libraries:
SparkFun-Passives: Licensing: CC v3.0 Share-Alike You are welcome to use this library for commercial purposes.
